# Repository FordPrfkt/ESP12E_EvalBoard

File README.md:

# ESP12E_EvalBoard
Evaluation Board for the ESP12E WiFi Board

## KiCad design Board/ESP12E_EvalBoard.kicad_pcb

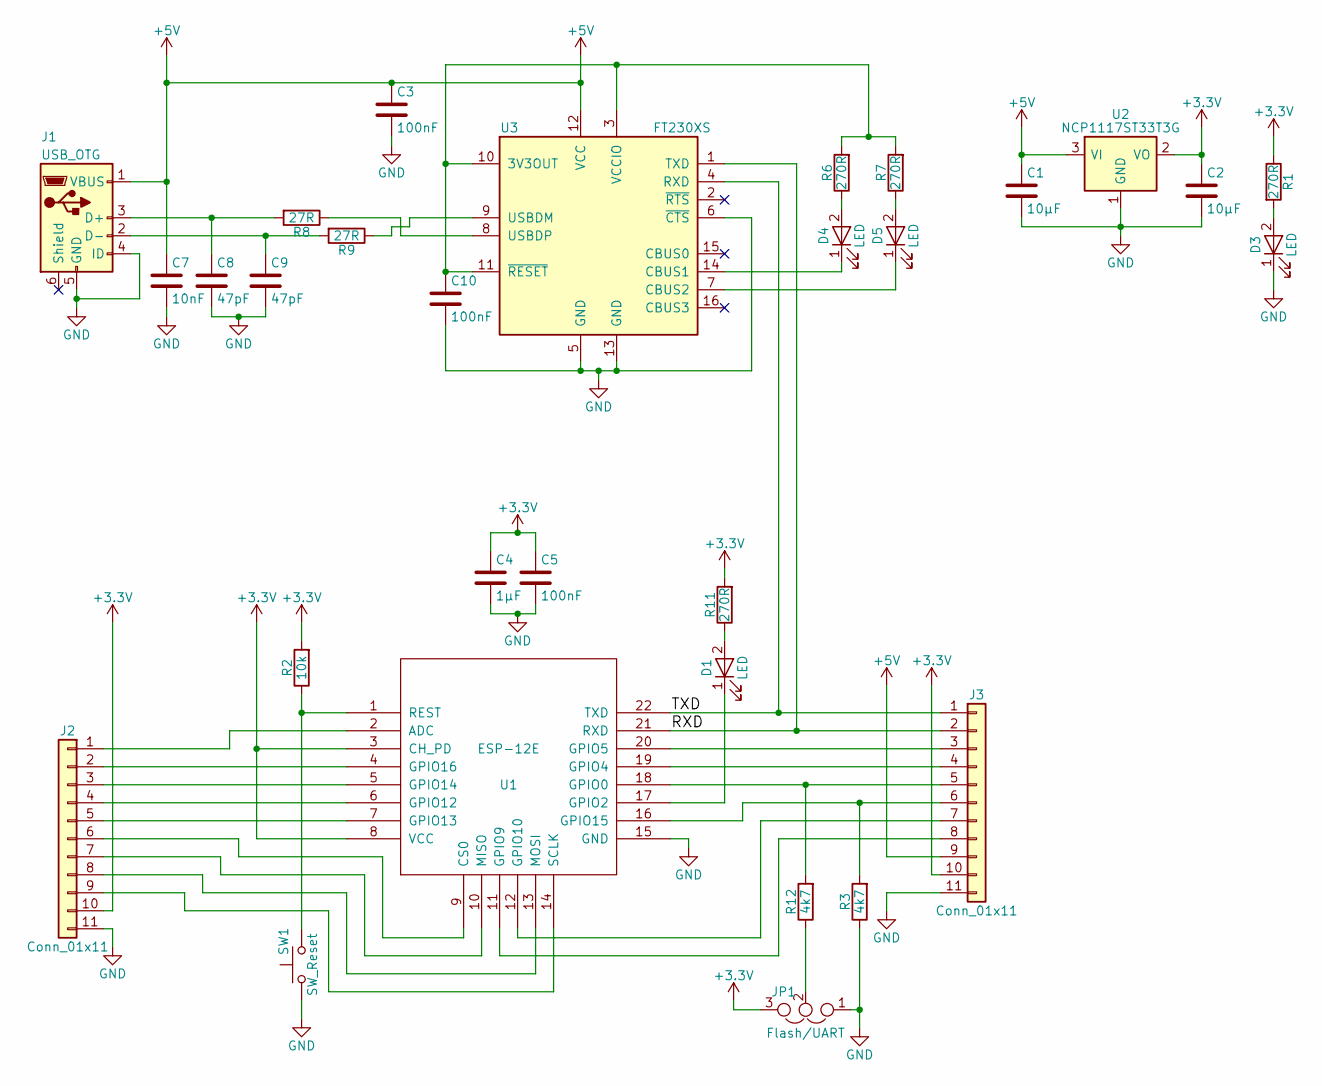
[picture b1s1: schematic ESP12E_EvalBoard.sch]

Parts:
C1, C2: 10µF; C_0805_HandSoldering
C3, C5, C10: 100nF; C_0805_HandSoldering
C4: 1µF; C_0805_HandSoldering
C7: 10nF; C_0805_HandSoldering
C8, C9: 47pF; C_0805_HandSoldering
D1, D3, D4, D5: LED; LED_0805_HandSoldering
J1: USB_OTG; USB_Mini-B
J2, J3: Conn_01x11; Pin_Header_Straight_1x11_Pitch2.54mm
JP1: Flash/UART; Pin_Header_Straight_1x03_Pitch2.54mm
R1, R6, R7, R11: 270R; R_0805_HandSoldering
R2: 10k; R_0805_HandSoldering
R3, R12: 4k7; R_0805_HandSoldering
R8, R9: 27R; R_0805_HandSoldering
SW1: SW_Reset; SW_SPST_B3S-1000
U1: ESP-12E
U2: NCP1117ST33T3G; SOT-223
U3: FT230XS; SSOP-16_5.3x6.2mm_Pitch0.65mm

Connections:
+3V3: C2.1, C4.1, C5.1, J2.10, J3.10, JP1.3, R1.1, R2.2, R11.2, U1.3 (CH_PD), U1.8 (VCC), U2.2 (VO)
+5V: C1.1, C3.1, C7.1, J1.1 (VBUS), J3.9, U2.3 (VI), U3.12 (VCC)
/RXD: J3.2, U1.21 (RXD), U3.1 (TXD)
/TXD: J3.1, U1.22 (TXD), U3.4 (RXD)
GND: C1.2, C2.2, C3.2, C4.2, C5.2, C7.2, C8.2, C9.2, C10.2, D3.1 (K), J1.4 (ID), J1.5 (GND), J2.11, J3.11, JP1.1, R3.1, SW1.1, U1.15 (GND), U2.1 (GND), U3.5 (GND), U3.6 (~CTS), U3.13 (GND)
unnamed: C8.1, J1.3 (D+), R8.2
unnamed: C9.1, J1.2 (D-), R9.2
unnamed: C10.1, R6.2, R7.2, U3.3 (VCCIO), U3.10 (3V3OUT), U3.11 (~RESET)
unnamed: D1.1 (K), U1.17 (GPIO2)
unnamed: D1.2 (A), R11.1
unnamed: D3.2 (A), R1.2
unnamed: D4.1 (K), U3.14 (CBUS1)
unnamed: D4.2 (A), R6.1
unnamed: D5.1 (K), U3.7 (CBUS2)
unnamed: D5.2 (A), R7.1
unnamed: J2.1, U1.2 (ADC)
unnamed: J2.2, U1.4 (GPIO16)
unnamed: J2.3, U1.5 (GPIO14)
unnamed: J2.4, U1.6 (GPIO12)
unnamed: J2.5, U1.7 (GPIO13)
unnamed: J2.6, U1.9 (CS0)
unnamed: J2.7, U1.10 (MISO)
unnamed: J2.8, U1.13 (MOSI)
unnamed: J2.9, U1.14 (SCLK)
unnamed: J3.3, U1.20 (GPIO5)
unnamed: J3.4, U1.19 (GPIO4)
unnamed: J3.5, R12.2, U1.18 (GPIO0)
unnamed: J3.6, R3.2, U1.16 (GPIO15)
unnamed: J3.7, U1.12 (GPIO10)
unnamed: J3.8, U1.11 (GPIO9)
unnamed: JP1.2, R12.1
unnamed: R2.1, SW1.2, U1.1 (REST)
unnamed: R8.1, U3.8 (USBDP)
unnamed: R9.1, U3.9 (USBDM)

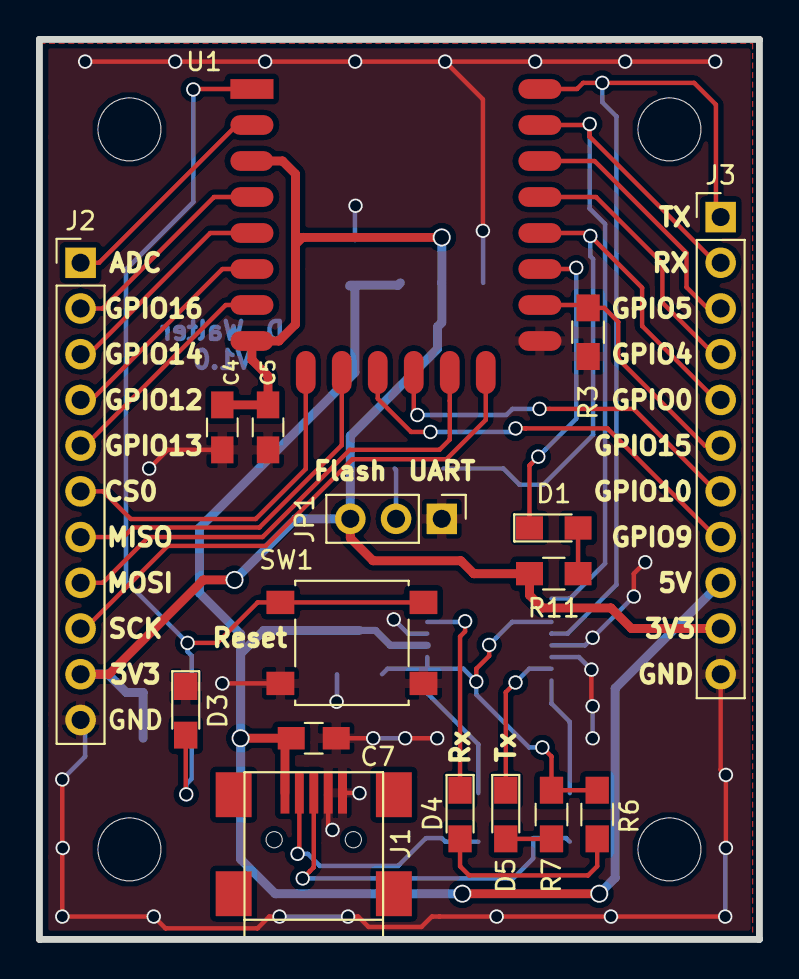
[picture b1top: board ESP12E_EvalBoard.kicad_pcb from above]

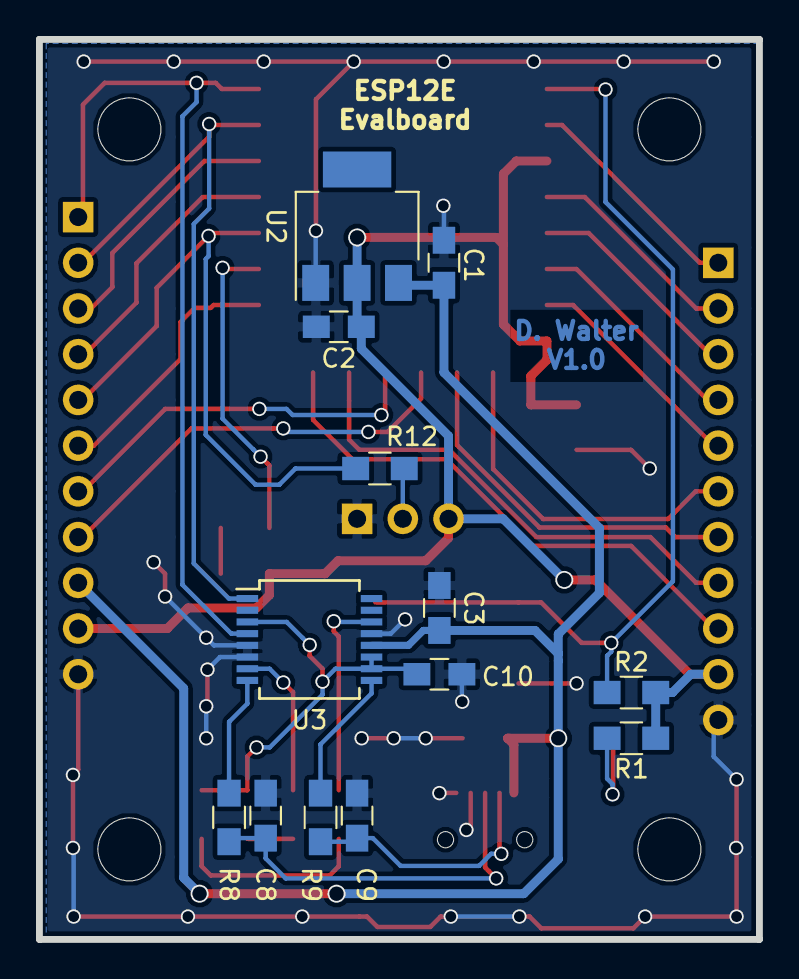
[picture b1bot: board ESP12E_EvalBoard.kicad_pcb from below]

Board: 2 copper layers, 40.0 x 50.0 mm, 30 parts (13 on the bottom side), 34 nets.

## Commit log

2018-02-11 Create LICENSE
2018-12-07 Production version
2018-12-09 Updated ignore list
